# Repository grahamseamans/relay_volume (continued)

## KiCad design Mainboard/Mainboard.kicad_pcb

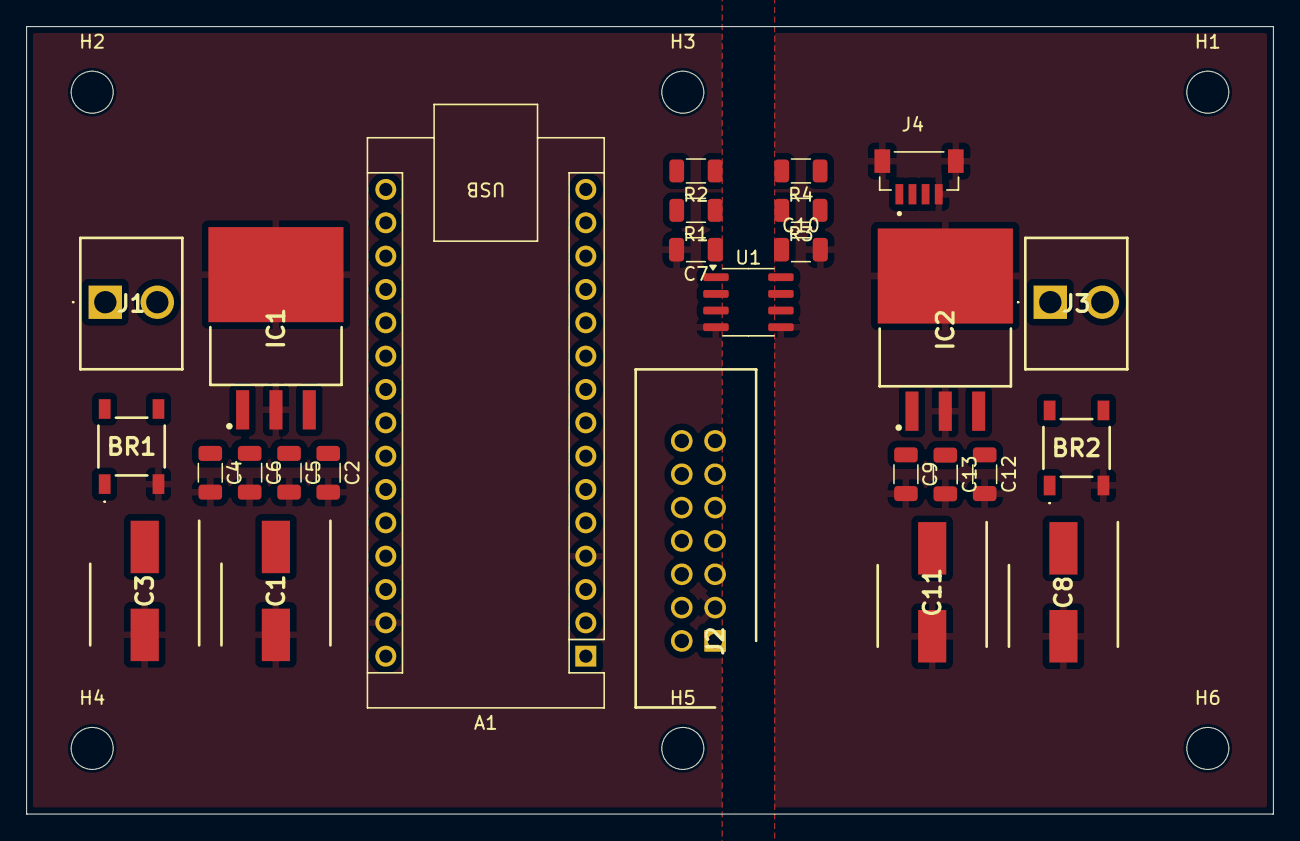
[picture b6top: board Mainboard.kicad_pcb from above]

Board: 2 copper layers, 95.0 x 60.0 mm, 33 parts (0 on the bottom side), 22 nets, no tracks yet.

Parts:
A1: Arduino_Nano_v3.x; Arduino_Nano
BR1, BR2: ABS8
C1, C3, C8, C11: UUD1V101MNL1GS; CAPAE830X1050N
C2, C4, C7, C9, C10: .1uf; C_1206_3216Metric
C5, C12: 10uf; C_1206_3216Metric
C6, C13: 1uf; C_1206_3216Metric
H1, H2, H3, H4, H5, H6: MountingHole; MountingHole_3.2mm_M3_ISO7380
IC1, IC2: MC7805BD2TR4G; TO254P1420X457-4N
J1, J3: 26-60-4023; 26604023
J2: BHR-14-VUA; SHDR14W64P254_2X7_2538X880X948P
J4: 4328; ADAFRUIT_4328
R1, R2, R3, R4: 1k; R_1206_3216Metric
U1: ISO1541; SOIC-8_3.9x4.9mm_P1.27mm

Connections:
+5V: A1.27 (+5V), C1.1 (+), C2.1, C5.1, C6.1, C7.1, IC1.3 (OUT), J2.1, R1.1, R2.1, U1.1 (VCC1)
+5V-iso: C10.1, C11.1 (+), C12.1, C13.1, IC2.3 (OUT), J4.1, R3.2, R4.2, U1.8 (VCC2)
GNDD: A1.4 (GND), A1.29 (GND), BR1.4 (-), C1.2 (-), C2.2, C3.2 (-), C4.2, C5.2, C6.2, C7.2, IC1.2 (GND_NOPAD), IC1.4 (GND_TAB), J2.3, U1.4 (GND1)
GNDI: BR2.4 (-), C8.2 (-), C9.2, C10.2, C11.2 (-), C12.2, C13.2, IC2.2 (GND_NOPAD), IC2.4 (GND_TAB), J4.4, J4.SH1 (SHIELD), J4.SH2 (SHIELD), U1.5 (GND2)
unnamed: BR1.1 (+), C3.1 (+), C4.1, IC1.1 (IN)
unnamed: BR1.2 (~_1), J1.1
unnamed: BR1.3 (~_2), J1.2
unnamed: BR2.1 (+), C8.1 (+), C9.1, IC2.1 (IN)
unnamed: BR2.2 (~_1), J3.1
unnamed: BR2.3 (~_2), J3.2
unnamed: J4.3, R4.1, U1.6 (SCL2)
unnamed: J4.2, R3.1, U1.7 (SDA2)
SCL: A1.24 (A5), R2.2, U1.3 (SCL1)
SDA: A1.23 (A4), R1.2, U1.2 (SDA1)
blank: A1.16 (D13), J2.7
data: A1.13 (D10), J2.13
enc_a: A1.9 (D6), J2.2
enc_b: A1.10 (D7), J2.4
enc_push: A1.11 (D8), J2.6
ir: A1.12 (D9), J2.14
sclk: A1.14 (D11), J2.11
xlat: A1.15 (D12), J2.9

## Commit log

2024-08-13 init
2024-08-14 seperated front panel board
2024-08-14 moving everything onto front panel, switching psu, no iso
2024-08-14 seperate psu, traco. All logic and such on front panel
2024-08-16 audio board, using rlxpassive base
2024-08-16 Switch panel seperate, going to integrate i2c onto volume now
2024-08-19 likely all done with v1, mainboard obsolete
2024-08-19 removed mainboard
2024-12-02 almost made 2040 raw
2024-12-02 pico front panel so easy
2024-12-02 somehow maybe done
2024-12-02 little neatening
2024-12-02 moved control to side, added electrolytic caps
2024-12-04 added output rca option
